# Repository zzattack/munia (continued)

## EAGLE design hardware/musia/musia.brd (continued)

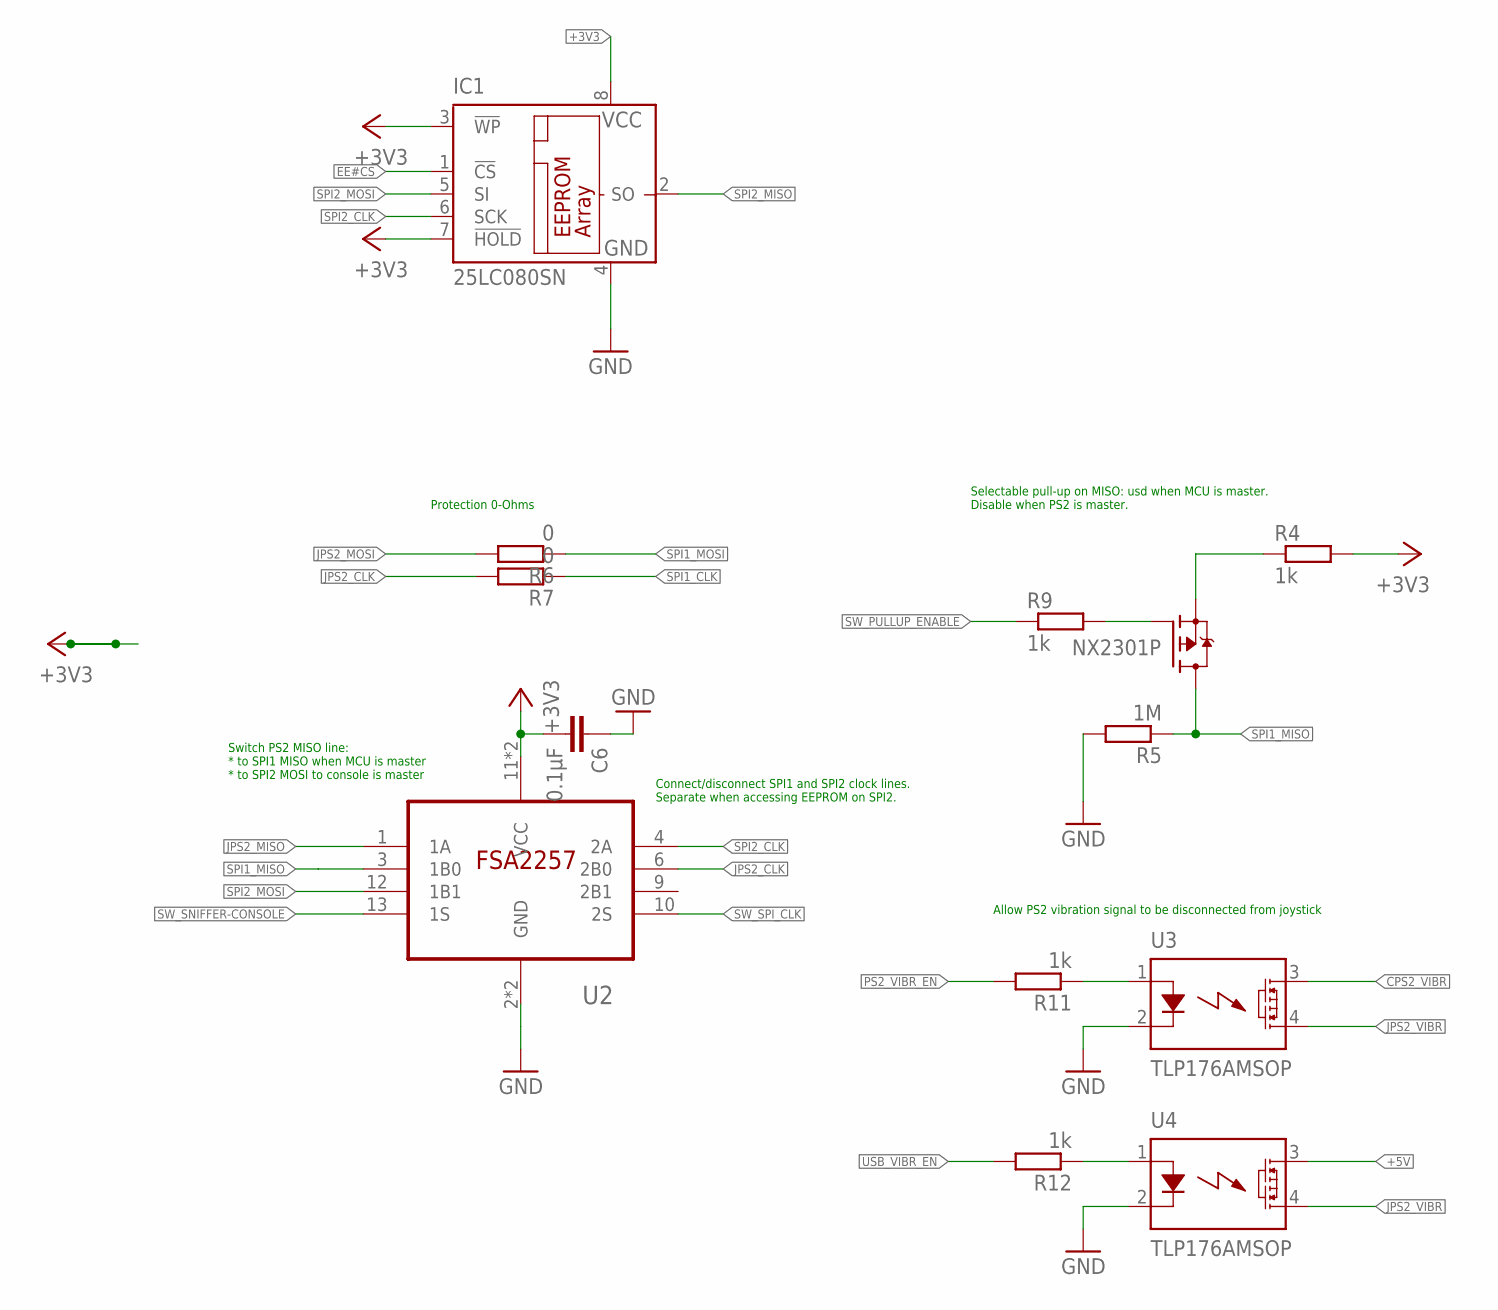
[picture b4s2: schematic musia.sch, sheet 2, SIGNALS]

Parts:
C6: 0.1µF; C0603
IC1: 25LC080SN; SO-08
R4, R9, R11, R12: 1k; R0603
R5: 1M; R0603
R6, R7: 0; R0603
U2: FSA2257; TSSOP14
U3, U4: TLP176AMSOP; SOP-4-2.54
U$3: NX2301P; SOT23

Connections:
+3V3: C6.2, IC1.3 (!WP), IC1.7 (!HOLD), IC1.8 (VCC), R4.2, U2.11 (VCC), U2.14 (VCC); also elsewhere on the board
+5V: U4.3 (D1); also elsewhere on the board
CPS2_VIBR: U3.3 (D1); also elsewhere on the board
EE#CS: IC1.1 (!CS); also elsewhere on the board
GND: C6.1, IC1.4 (GND), R5.2, U2.2 (GND), U2.5 (GND), U3.2 (K), U4.2 (K); also elsewhere on the board
JPS2_CLK: R7.2, U2.6 (2B0); also elsewhere on the board
JPS2_MISO: U2.1 (1A); also elsewhere on the board
JPS2_MOSI: R6.2; also elsewhere on the board
JPS2_VIBR: U3.4 (D2), U4.4 (D2); also elsewhere on the board
unnamed: R4.1, U$3.2 (S)
unnamed: R11.1, U3.1 (A)
unnamed: R9.2, U$3.1 (G)
unnamed: R12.1, U4.1 (A)
PS2_VIBR_EN: R11.2; also elsewhere on the board
SPI1_CLK: R7.1; also elsewhere on the board
SPI1_MISO: R5.1, U2.3 (1B0), U$3.3 (D); also elsewhere on the board
SPI1_MOSI: R6.1; also elsewhere on the board
SPI2_CLK: IC1.6 (SCK), U2.4 (2A); also elsewhere on the board
SPI2_MISO: IC1.2 (SO); also elsewhere on the board
SPI2_MOSI: IC1.5 (SI), U2.12 (1B1); also elsewhere on the board
SW_PULLUP_ENABLE: R9.1; also elsewhere on the board
SW_SNIFFER-CONSOLE: U2.13 (1S); also elsewhere on the board
SW_SPI_CLK: U2.10 (2S); also elsewhere on the board
USB_VIBR_EN: R12.2; also elsewhere on the board

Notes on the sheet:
Allow PS2 vibration signal to be disconnected from joystick
Selectable pull-up on MISO: usd when MCU is master. Disable when PS2 is master.
Protection 0-Ohms
Switch PS2 MISO line: * to SPI1 MISO when MCU is master * to SPI2 MOSI to console is master
Connect/disconnect SPI1 and SPI2 clock lines. Separate when accessing EEPROM on SPI2.

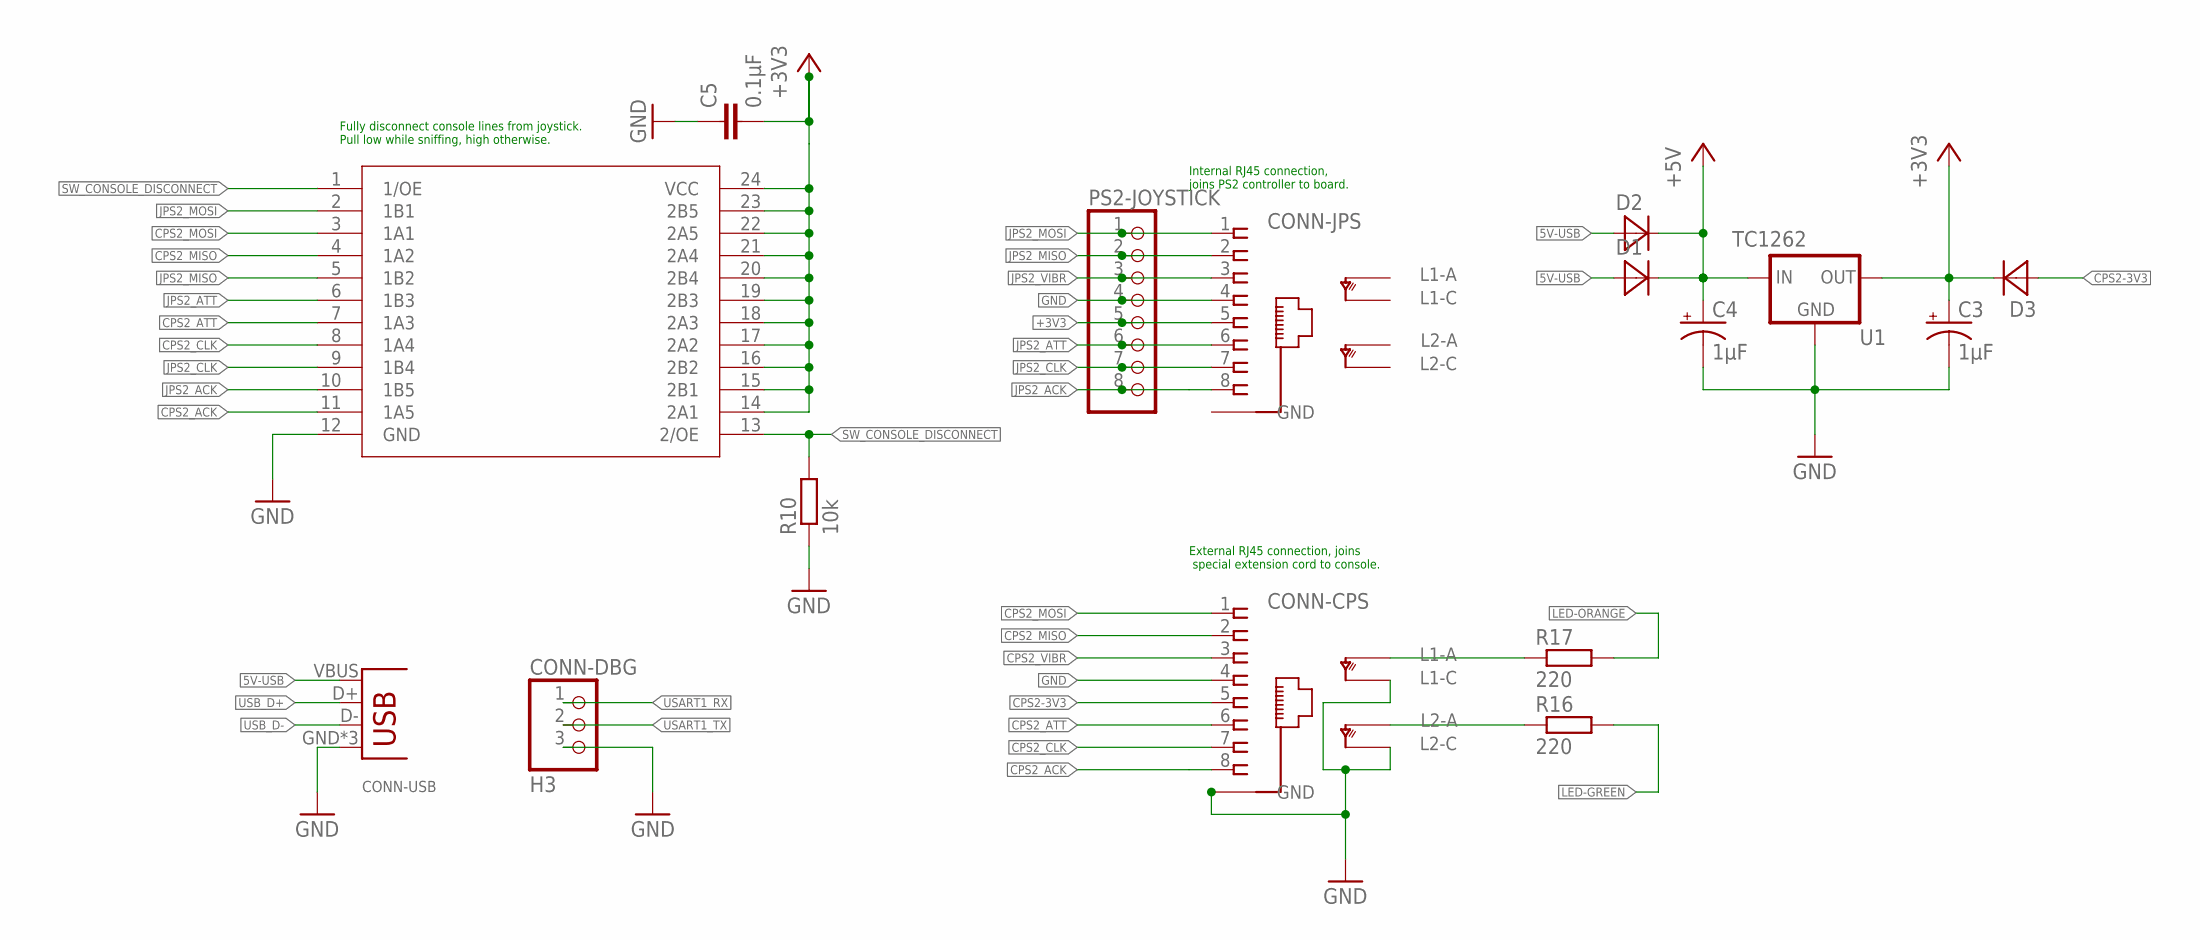
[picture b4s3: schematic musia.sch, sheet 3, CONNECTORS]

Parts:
C3, C4: 1µF; EIA3216
C5: 0.1µF; C0603
CONN-CPS: RJ45-NIELS
CONN-DBG: H3; 1X03
CONN-JPS: RJ45-NIELS
CONN-USB: USB-B-FEMALE; USB-B-H
D1, D2, D3: MBR120VLSFT1G; SOD123
PS2-JOYSTICK: PINHD-1X8; 1X08
R10: 10k; R0603
R16, R17: 220; R0603
U1: TC1262; SOT230P700X180-4N
U$2: SN74CB3Q3384; SSOP24

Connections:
5V-USB: CONN-USB.VBUS, D1.2 (A), D2.2 (A); also elsewhere on the board
+3V3: C3.A (+), C5.2, CONN-JPS.5, D3.1 (C), PS2-JOYSTICK.5, U1.3 (OUT), U$2.14 (2A1), U$2.15 (2B1), U$2.16 (2B2), U$2.17 (2A2), U$2.18 (2A3), U$2.19 (2B3), U$2.20 (2B4), U$2.21 (2A4), U$2.22 (2A5), U$2.23 (2B5), U$2.24 (VCC); also elsewhere on the board
+5V: C4.A (+), D1.1 (C), D2.1 (C), U1.1 (IN); also elsewhere on the board
CPS2-3V3: CONN-CPS.5, D3.2 (A)
CPS2_ACK: CONN-CPS.8, U$2.11 (1A5); also elsewhere on the board
CPS2_ATT: CONN-CPS.6, U$2.7 (1A3); also elsewhere on the board
CPS2_CLK: CONN-CPS.7, U$2.8 (1A4); also elsewhere on the board
CPS2_MISO: CONN-CPS.2, U$2.4 (1A2); also elsewhere on the board
CPS2_MOSI: CONN-CPS.1, U$2.3 (1A1); also elsewhere on the board
CPS2_VIBR: CONN-CPS.3; also elsewhere on the board
GND: C3.C (-), C4.C (-), C5.1, CONN-CPS.4, CONN-CPS.GND@5 (GND), CONN-CPS.GND@6 (GND), CONN-CPS.LED-GREEN-C (L2C), CONN-CPS.LED-ORANGE-C (L1C), CONN-DBG.3, CONN-JPS.4, CONN-JPS.GND@5 (GND), CONN-JPS.GND@6 (GND), CONN-USB.GND, CONN-USB.GND@1 (GND), CONN-USB.GND@2 (GND), PS2-JOYSTICK.4, R10.1, U1.2 (GND), U1.4 (GND), U$2.12 (GND); also elsewhere on the board
JPS2_ACK: CONN-JPS.8, PS2-JOYSTICK.8, U$2.10 (1B5); also elsewhere on the board
JPS2_ATT: CONN-JPS.6, PS2-JOYSTICK.6, U$2.6 (1B3); also elsewhere on the board
JPS2_CLK: CONN-JPS.7, PS2-JOYSTICK.7, U$2.9 (1B4); also elsewhere on the board
JPS2_MISO: CONN-JPS.2, PS2-JOYSTICK.2, U$2.5 (1B2); also elsewhere on the board
JPS2_MOSI: CONN-JPS.1, PS2-JOYSTICK.1, U$2.2 (1B1); also elsewhere on the board
JPS2_VIBR: CONN-JPS.3, PS2-JOYSTICK.3; also elsewhere on the board
LED-GREEN: R16.2; also elsewhere on the board
LED-ORANGE: R17.2; also elsewhere on the board
unnamed: CONN-CPS.LED-ORANGE-A (L1A), R17.1
unnamed: CONN-CPS.LED-GREEN-A (L2A), R16.1
SW_CONSOLE_DISCONNECT: R10.2, U$2.1 (1/OE), U$2.13 (2/OE); also elsewhere on the board
USART1_RX: CONN-DBG.1; also elsewhere on the board
USART1_TX: CONN-DBG.2; also elsewhere on the board
USB_D+: CONN-USB.D+; also elsewhere on the board
USB_D-: CONN-USB.D-; also elsewhere on the board

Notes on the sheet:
Fully disconnect console lines from joystick. Pull low while sniffing, high otherwise.
External RJ45 connection, joins special extension cord to console.
Internal RJ45 connection, joins PS2 controller to board.

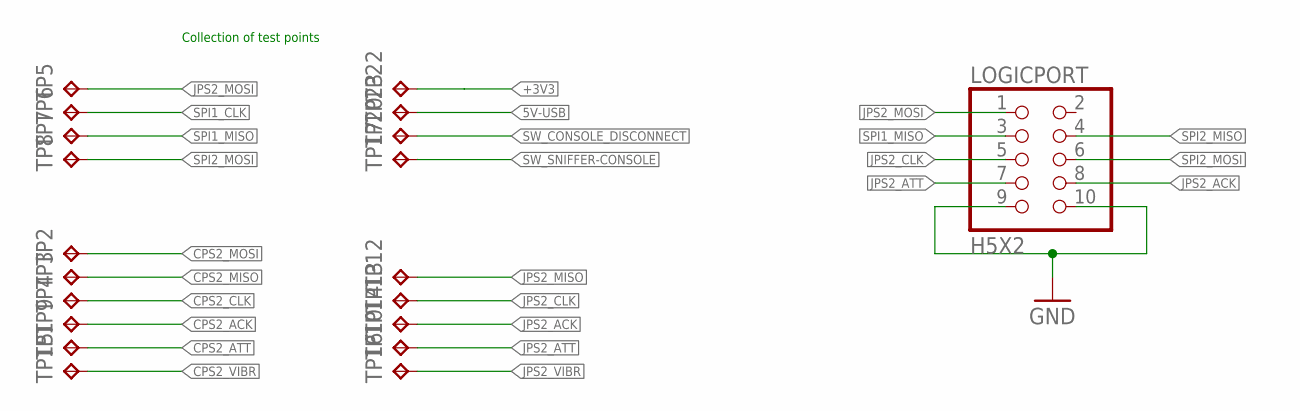
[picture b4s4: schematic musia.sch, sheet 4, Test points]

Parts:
LOGICPORT: H5X2; 2X05
TP1, TP2, TP3, TP4, TP5, TP6, TP7, TP8, TP9, TP10, TP12, TP13, TP14, TP15, TP16, TP17, TP20, TP22, TP23: TPB1,27; B1,27

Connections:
5V-USB: TP23.TP; also elsewhere on the board
+3V3: TP22.TP; also elsewhere on the board
CPS2_ACK: TP9.TP; also elsewhere on the board
CPS2_ATT: TP1.TP; also elsewhere on the board
CPS2_CLK: TP4.TP; also elsewhere on the board
CPS2_MISO: TP3.TP; also elsewhere on the board
CPS2_MOSI: TP2.TP; also elsewhere on the board
CPS2_VIBR: TP15.TP; also elsewhere on the board
GND: LOGICPORT.9, LOGICPORT.10; also elsewhere on the board
JPS2_ACK: LOGICPORT.8, TP14.TP; also elsewhere on the board
JPS2_ATT: LOGICPORT.7, TP10.TP; also elsewhere on the board
JPS2_CLK: LOGICPORT.5, TP13.TP; also elsewhere on the board
JPS2_MISO: TP12.TP; also elsewhere on the board
JPS2_MOSI: LOGICPORT.1, TP5.TP; also elsewhere on the board
JPS2_VIBR: TP16.TP; also elsewhere on the board
SPI1_CLK: TP6.TP; also elsewhere on the board
SPI1_MISO: LOGICPORT.3, TP7.TP; also elsewhere on the board
SPI2_MISO: LOGICPORT.4; also elsewhere on the board
SPI2_MOSI: LOGICPORT.6, TP8.TP; also elsewhere on the board
SW_CONSOLE_DISCONNECT: TP20.TP; also elsewhere on the board
SW_SNIFFER-CONSOLE: TP17.TP; also elsewhere on the board

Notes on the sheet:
Collection of test points

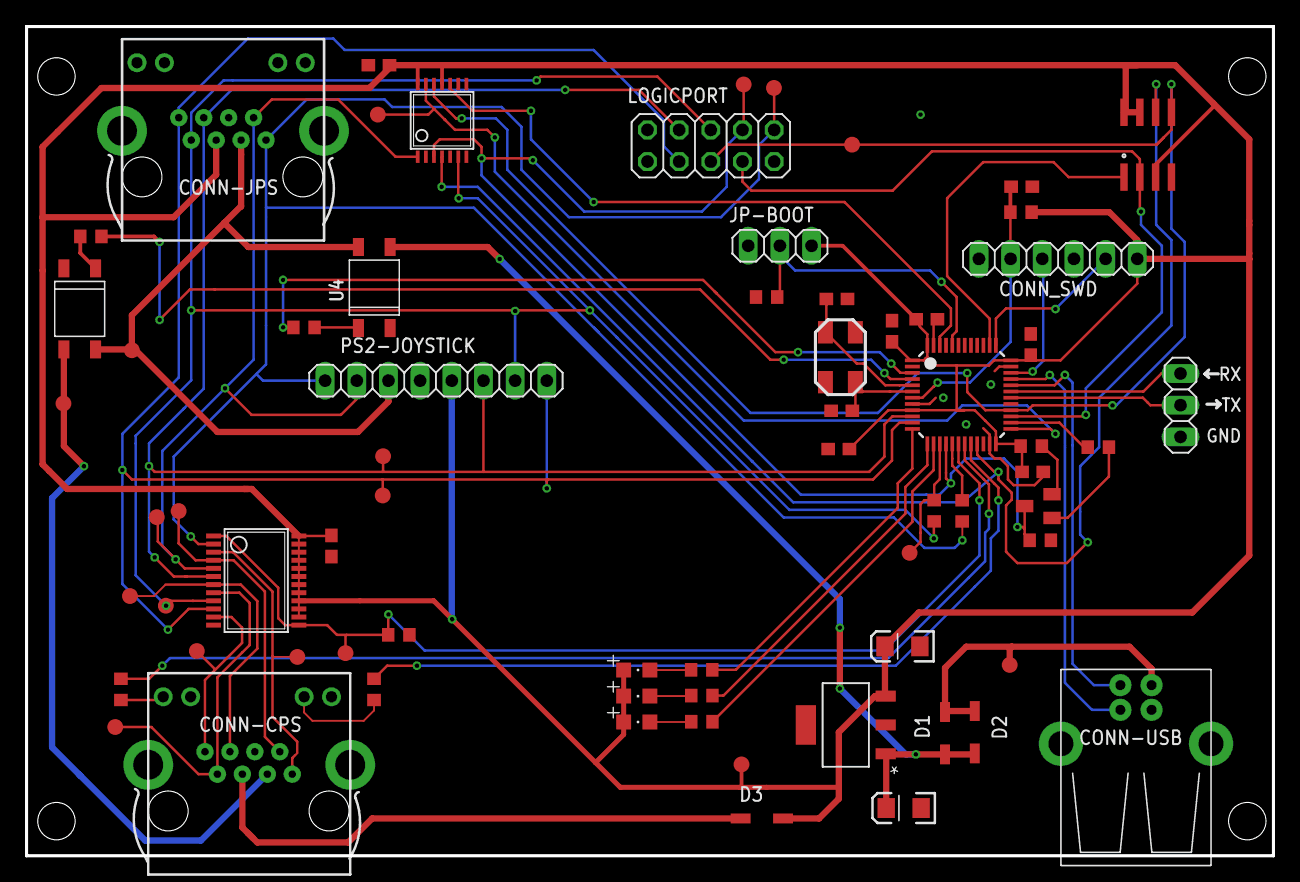
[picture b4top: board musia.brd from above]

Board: 2 copper layers, 100.0 x 66.5 mm, 69 parts (0 on the bottom side), 54 nets.

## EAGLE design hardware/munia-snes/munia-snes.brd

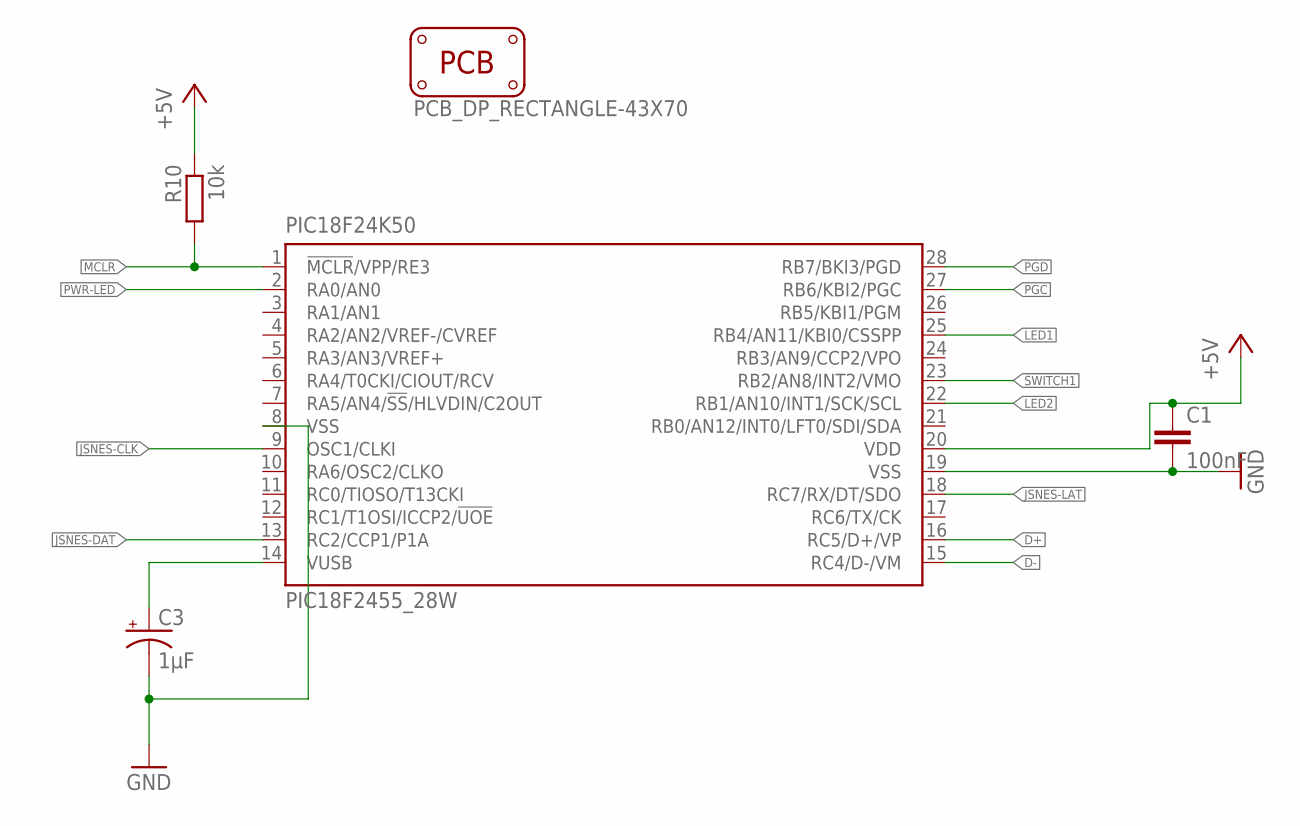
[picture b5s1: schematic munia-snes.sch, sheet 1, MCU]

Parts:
C1: 100nF; C0603
C3: 1µF; EIA3216
PCB1: PCB_DP_RECTANGLE-43X70; DP7043_V1
PIC18F24K50: PIC18F2455_28W; SO28W
R10: 10k; R0603

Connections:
+5V: C1.1, PIC18F24K50.20 (VDD), R10.1; also elsewhere on the board
D+: PIC18F24K50.16 (RC5/D+/VP); also elsewhere on the board
D-: PIC18F24K50.15 (RC4/D-/VM); also elsewhere on the board
GND: C1.2, C3.C (-), PIC18F24K50.8 (VSS), PIC18F24K50.19 (VSS); also elsewhere on the board
JSNES-CLK: PIC18F24K50.9 (OSC1/CLKI); also elsewhere on the board
JSNES-DAT: PIC18F24K50.13 (RC2/CCP1/P1A); also elsewhere on the board
JSNES-LAT: PIC18F24K50.18 (RC7/RX/DT/SDO); also elsewhere on the board
LED1: PIC18F24K50.25 (RB4/AN11/KBI0/CSSPP); also elsewhere on the board
LED2: PIC18F24K50.22 (RB1/AN10/INT1/SCK/SCL); also elsewhere on the board
MCLR: PIC18F24K50.1 (!MCLR!/VPP/RE3), R10.2; also elsewhere on the board
unnamed: C3.A (+), PIC18F24K50.14 (VUSB)
PGC: PIC18F24K50.27 (RB6/KBI2/PGC); also elsewhere on the board
PGD: PIC18F24K50.28 (RB7/BKI3/PGD); also elsewhere on the board
PWR-LED: PIC18F24K50.2 (RA0/AN0); also elsewhere on the board
SWITCH1: PIC18F24K50.23 (RB2/AN8/INT2/VMO); also elsewhere on the board

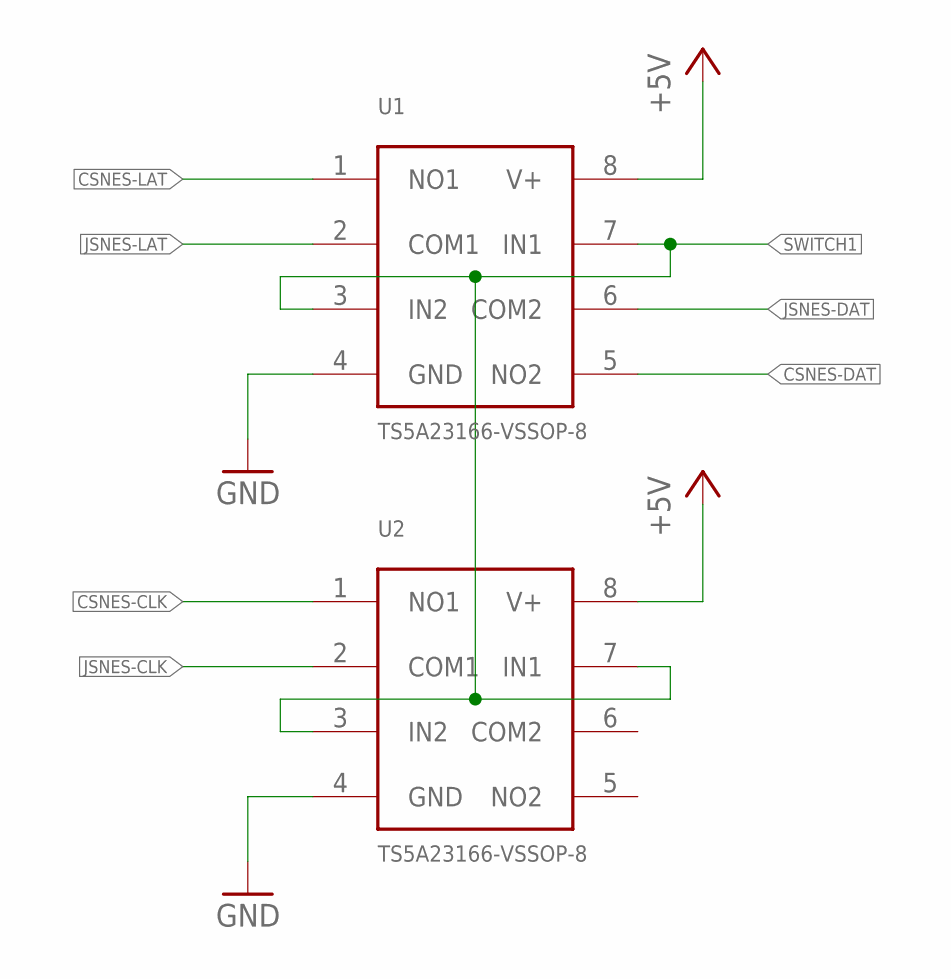
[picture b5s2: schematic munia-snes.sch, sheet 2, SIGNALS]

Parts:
U1, U2: TS5A23166-VSSOP-8; SOT765

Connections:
+5V: U1.8 (V+), U2.8 (V+); also elsewhere on the board
CSNES-CLK: U2.1 (NO1); also elsewhere on the board
CSNES-DAT: U1.5 (NO2); also elsewhere on the board
CSNES-LAT: U1.1 (NO1); also elsewhere on the board
GND: U1.4 (GND), U2.4 (GND); also elsewhere on the board
JSNES-CLK: U2.2 (COM1); also elsewhere on the board
JSNES-DAT: U1.6 (COM2); also elsewhere on the board
JSNES-LAT: U1.2 (COM1); also elsewhere on the board
SWITCH1: U1.3 (IN2), U1.7 (IN1), U2.3 (IN2), U2.7 (IN1); also elsewhere on the board

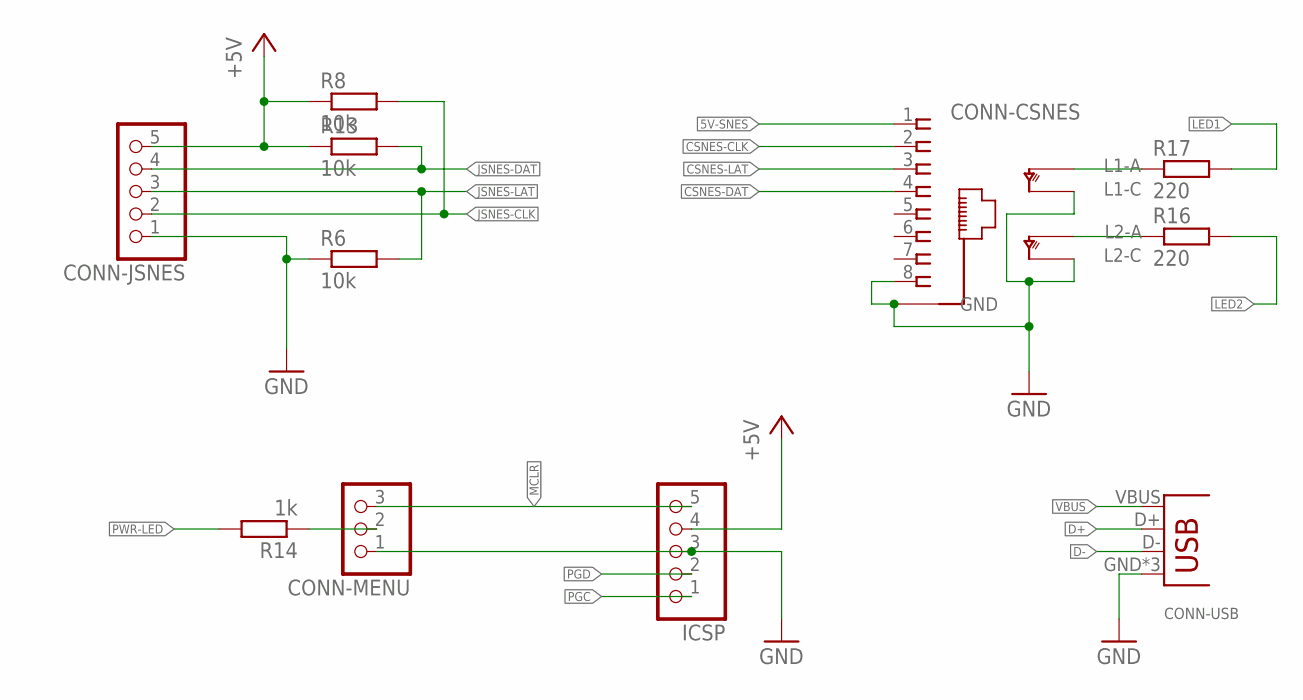
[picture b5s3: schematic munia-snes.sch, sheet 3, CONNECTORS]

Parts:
CONN-CSNES: RJ45-NIELS
CONN-JSNES: PINHD-1X5; 1X05
CONN-MENU: PINHD-1X3; 1X03
CONN-USB: USB-B-NIELS; USB-B-H
ICSP: PINHD-1X5; 1X05
R6, R8, R13: 10k; R0603
R14: 1k; R0603
R16, R17: 220; R0603

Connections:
5V-SNES: CONN-CSNES.1; also elsewhere on the board
+5V: CONN-JSNES.5, ICSP.4, R8.1, R13.1; also elsewhere on the board
CSNES-CLK: CONN-CSNES.2; also elsewhere on the board
CSNES-DAT: CONN-CSNES.4; also elsewhere on the board
CSNES-LAT: CONN-CSNES.3; also elsewhere on the board
D+: CONN-USB.D+; also elsewhere on the board
D-: CONN-USB.D-; also elsewhere on the board
GND: CONN-CSNES.8, CONN-CSNES.GND@5 (GND), CONN-CSNES.GND@6 (GND), CONN-CSNES.LED-GREEN-C (L2C), CONN-CSNES.LED-ORANGE-C (L1C), CONN-JSNES.1, CONN-MENU.1, CONN-USB.GND, CONN-USB.GND@1 (GND), CONN-USB.GND@2 (GND), ICSP.3, R6.1; also elsewhere on the board
JSNES-CLK: CONN-JSNES.2, R8.2; also elsewhere on the board
JSNES-DAT: CONN-JSNES.4, R13.2; also elsewhere on the board
JSNES-LAT: CONN-JSNES.3, R6.2; also elsewhere on the board
LED1: R17.2; also elsewhere on the board
LED2: R16.2; also elsewhere on the board
MCLR: CONN-MENU.3, ICSP.5; also elsewhere on the board
unnamed: CONN-MENU.2, R14.1
unnamed: CONN-CSNES.LED-ORANGE-A (L1A), R17.1
unnamed: CONN-CSNES.LED-GREEN-A (L2A), R16.1
PGC: ICSP.1; also elsewhere on the board
PGD: ICSP.2; also elsewhere on the board
PWR-LED: R14.2; also elsewhere on the board
VBUS: CONN-USB.VBUS; also elsewhere on the board

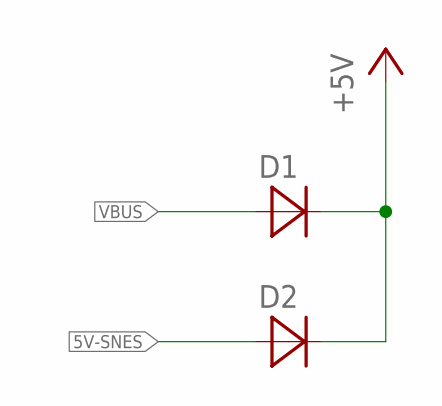
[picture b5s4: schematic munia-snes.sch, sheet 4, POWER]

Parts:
D1, D2: MBR120VLSFT1G; SOD123

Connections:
5V-SNES: D2.2 (A); also elsewhere on the board
+5V: D1.1 (C), D2.1 (C); also elsewhere on the board
VBUS: D1.2 (A); also elsewhere on the board

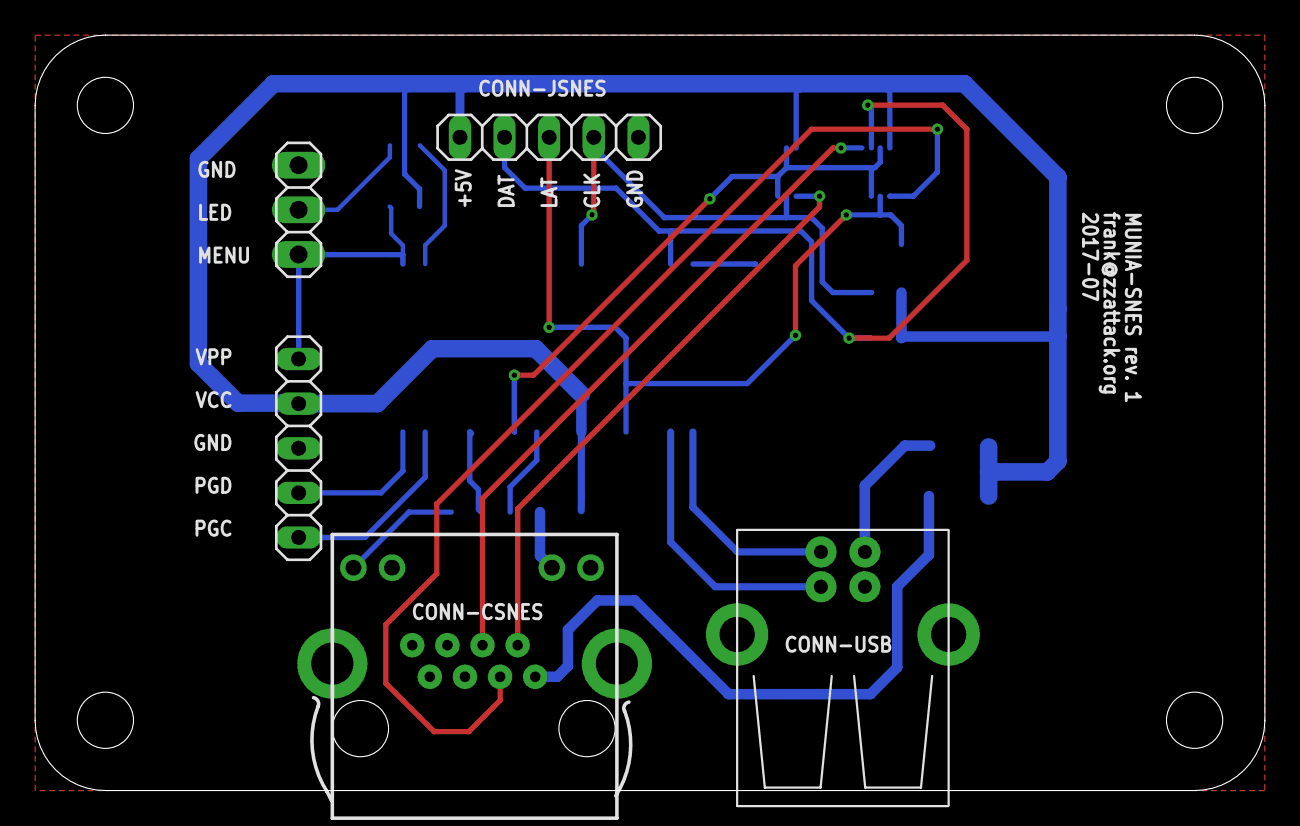
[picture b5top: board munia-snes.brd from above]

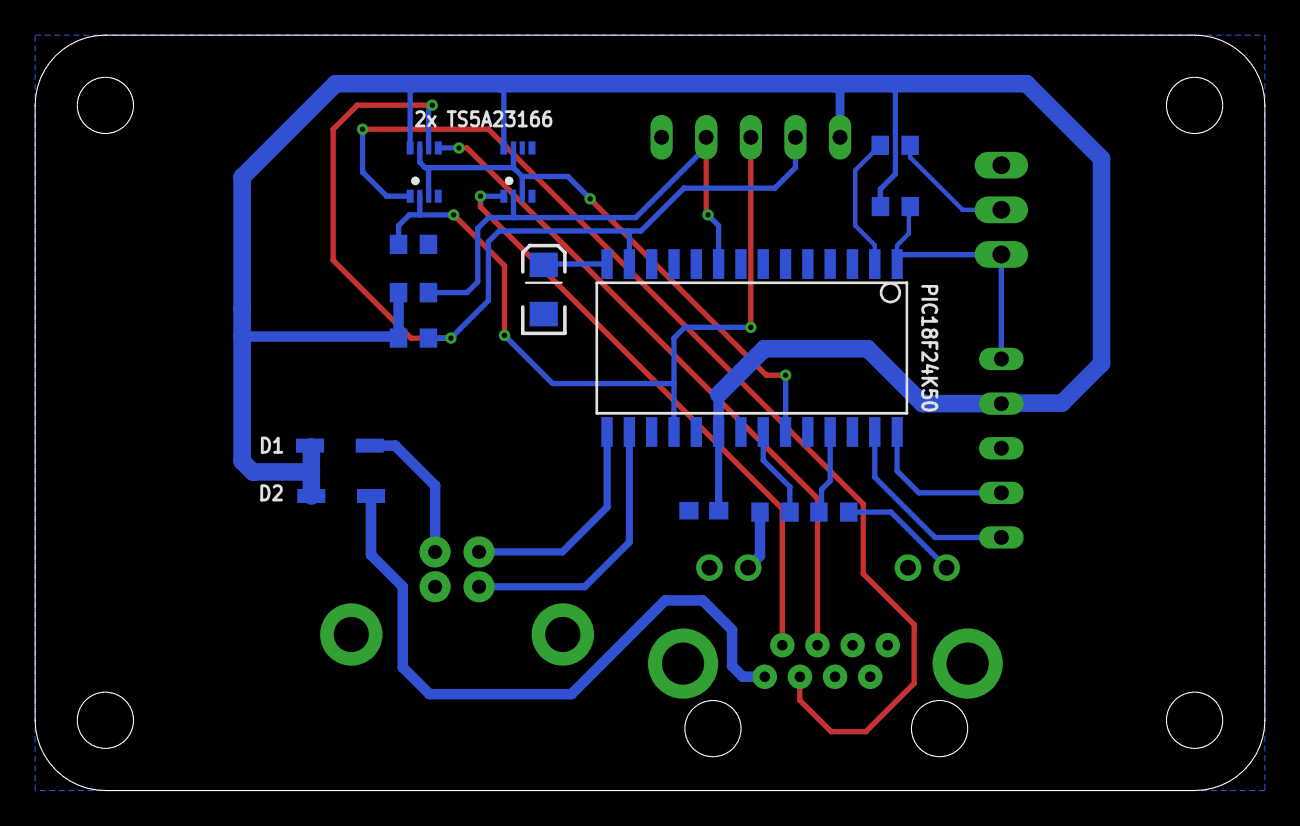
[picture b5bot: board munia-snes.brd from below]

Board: 2 copper layers, 70.0 x 43.0 mm, 20 parts (14 on the bottom side), 23 nets.

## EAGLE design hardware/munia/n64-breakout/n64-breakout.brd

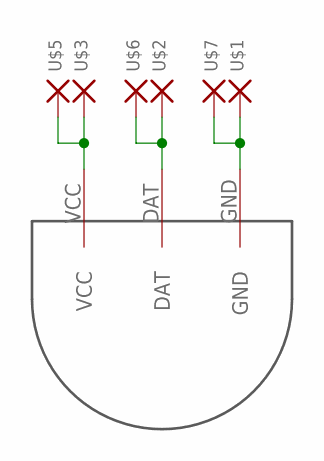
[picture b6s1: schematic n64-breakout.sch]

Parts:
U$1, U$2, U$3, U$5, U$6, U$7: SMDPADSMD6080; SMD6080
U$4: N64-CONNECTOR

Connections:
DAT: U$2.P$1, U$4.DAT, U$6.P$1
GND: U$1.P$1, U$4.GND, U$7.P$1
VCC: U$3.P$1, U$4.VCC, U$5.P$1

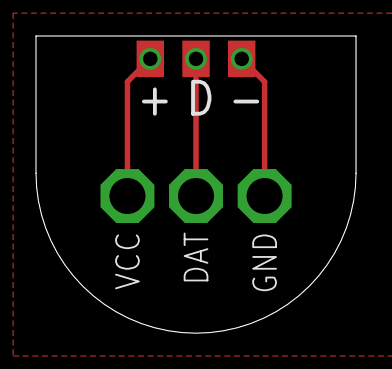
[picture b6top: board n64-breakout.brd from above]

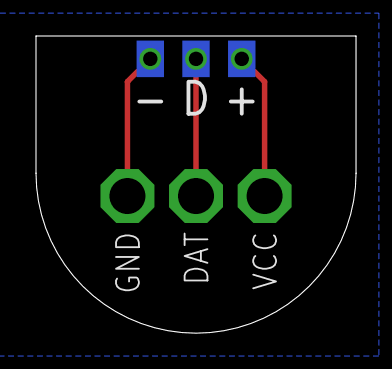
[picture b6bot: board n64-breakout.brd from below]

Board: 2 copper layers, 17.8 x 16.5 mm, 7 parts (4 on the bottom side), 3 nets.

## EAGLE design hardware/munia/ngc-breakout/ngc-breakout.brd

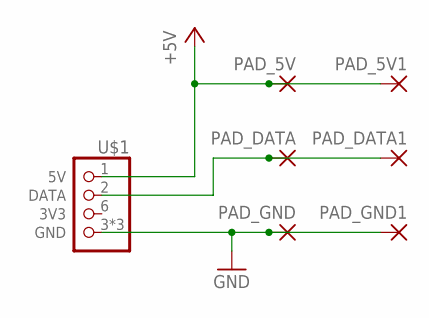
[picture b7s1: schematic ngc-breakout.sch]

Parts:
PAD_5V, PAD_5V1: SMD2; SMD1,27-2,54
PAD_DATA, PAD_DATA1: SMD2; SMD1,27-2,54
PAD_GND, PAD_GND1: SMD2; SMD1,27-2,54
U$1: NGC-CONNECTORGC-CONN2; NGC-CONNECTOR

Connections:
+5V: PAD_5V.1, PAD_5V1.1, U$1.1 (5V)
GND: PAD_GND.1, PAD_GND1.1, U$1.3 (GND), U$1.4 (GND), U$1.7 (GND)
unnamed: PAD_DATA.1, PAD_DATA1.1, U$1.2 (DATA)

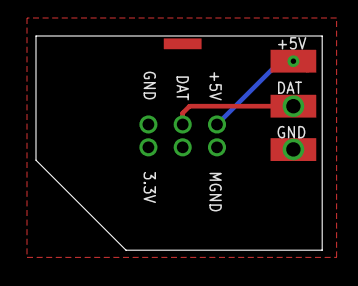
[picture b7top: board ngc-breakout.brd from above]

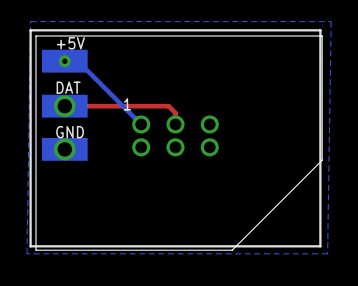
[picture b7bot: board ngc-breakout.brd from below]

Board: 2 copper layers, 15.9 x 11.9 mm, 7 parts (4 on the bottom side), 3 nets.
